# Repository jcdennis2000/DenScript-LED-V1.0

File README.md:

# DenScript-LED-V1.0

The DenScript LED (Light Emitting Diode) is a standard 5mm LED, housed in a convenient package together with a current limiting resistor, that allows it to be easily attached to projects, with our DenScript colour coded headers to make wiring far easier! Simply connect the RED pin to positive voltage (VCC), the BLACK pin to negative voltage (GND) and the WHITE pin to an output pin on your micro controller or development board!

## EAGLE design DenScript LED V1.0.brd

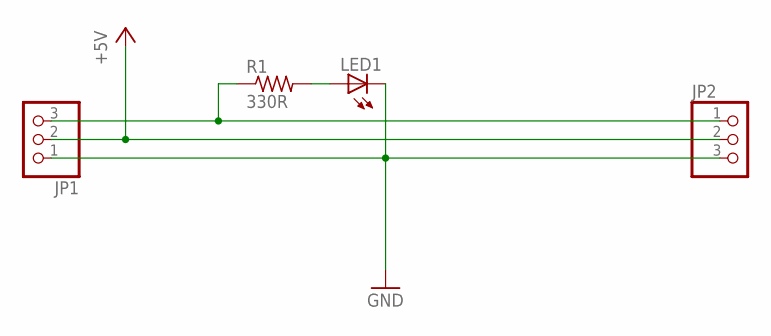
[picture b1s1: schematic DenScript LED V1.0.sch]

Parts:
JP1, JP2: PINHD-1X3; 1X03
LED1: LED5MM
R1: 330R; R0603

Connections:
+5V: JP1.2, JP2.2
GND: JP1.1, JP2.3, LED1.K (C)
unnamed: JP1.3, JP2.1, R1.1
unnamed: LED1.A, R1.2

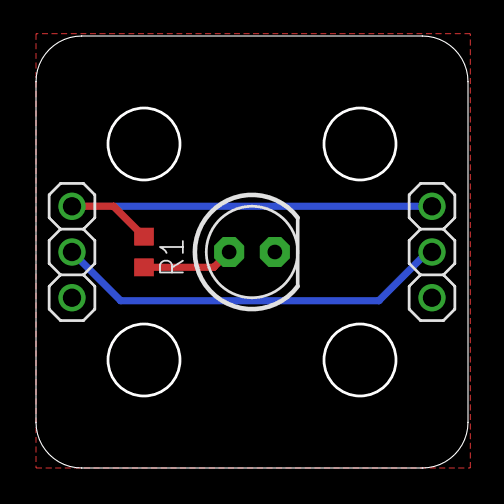
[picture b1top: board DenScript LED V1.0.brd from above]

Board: 2 copper layers, 23.8 x 23.8 mm, 4 parts (0 on the bottom side), 4 nets.

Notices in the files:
DenScript LED V1.0.brd:
Dennistries Ltd (c) 2019
